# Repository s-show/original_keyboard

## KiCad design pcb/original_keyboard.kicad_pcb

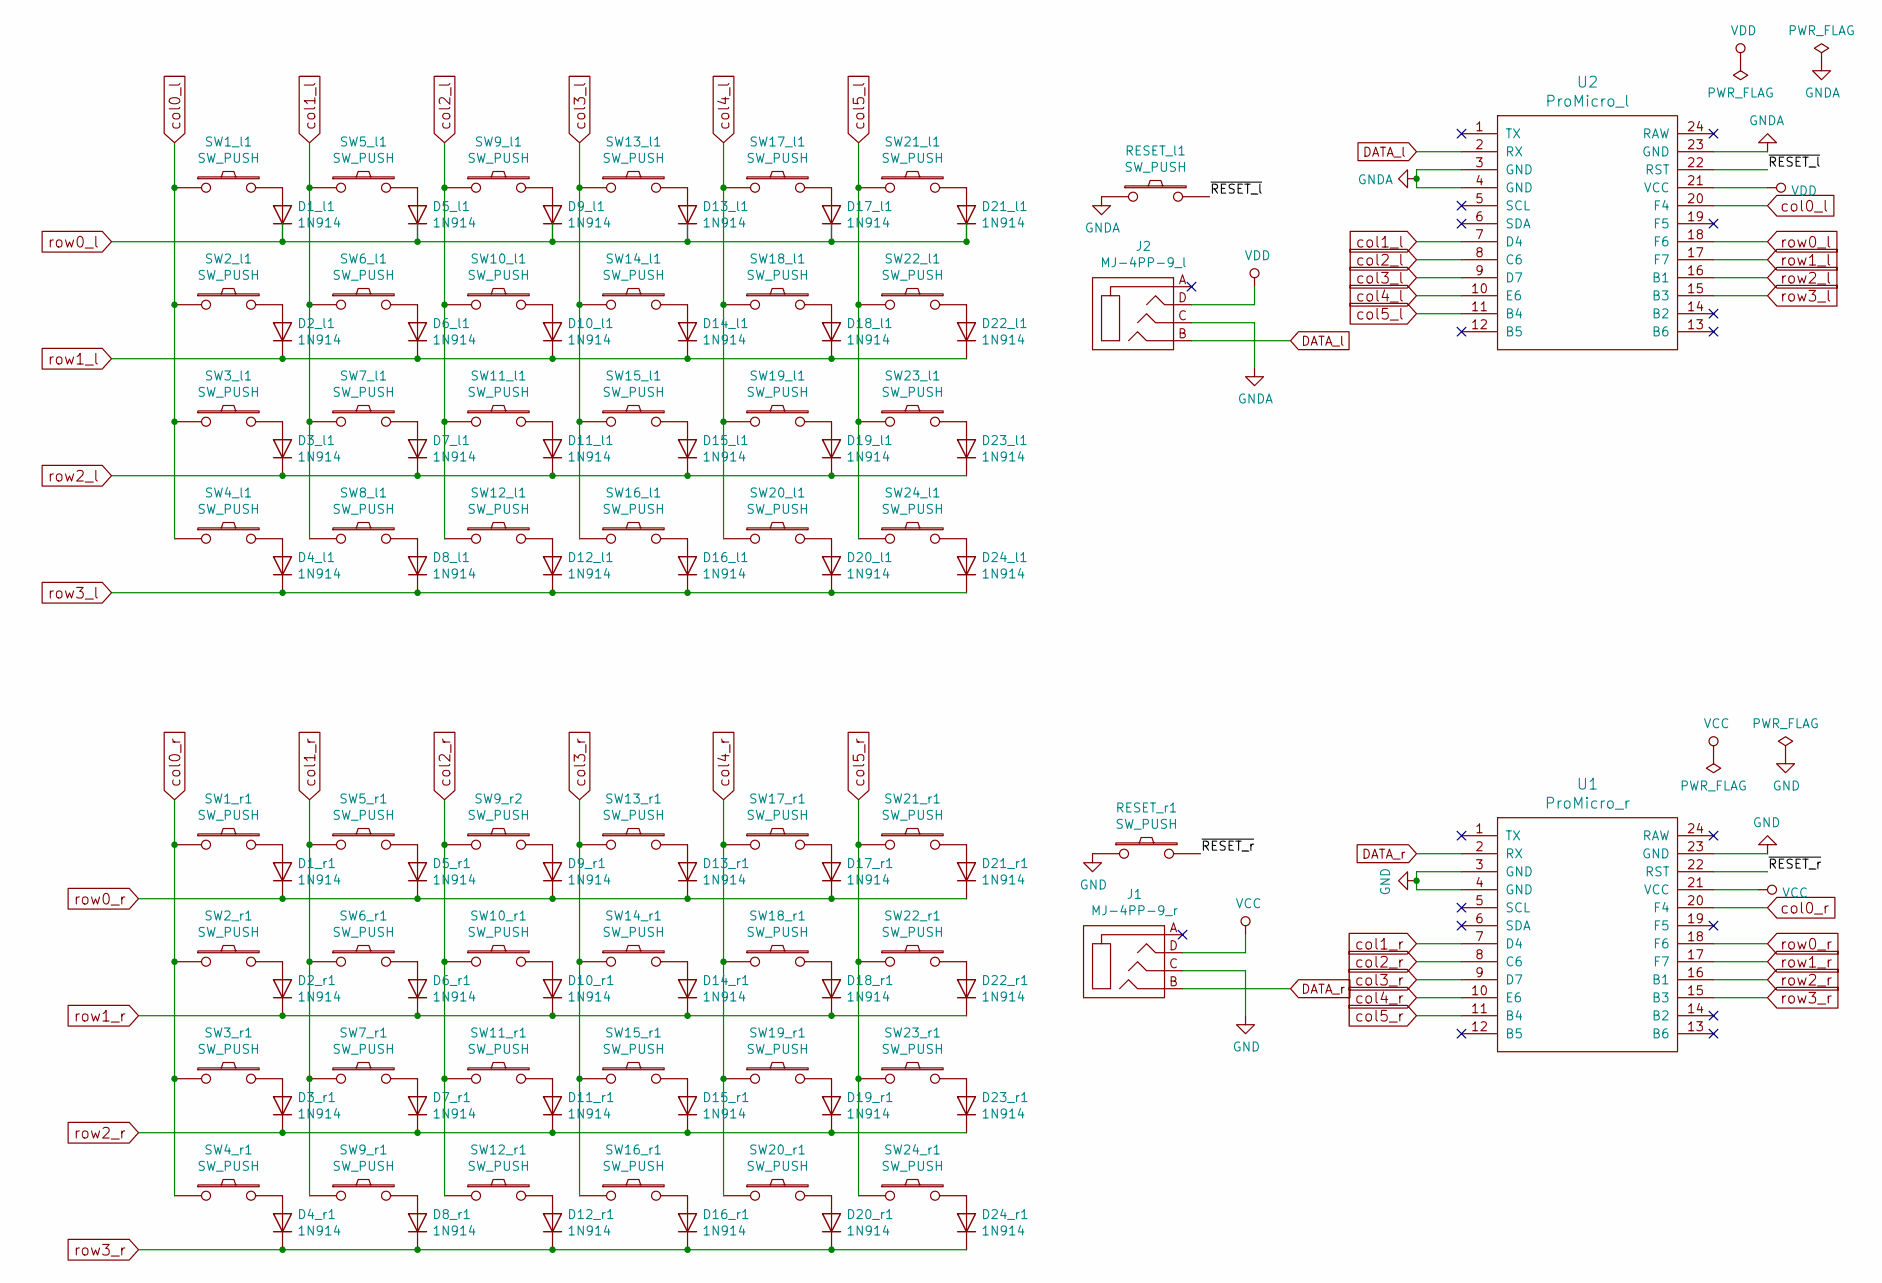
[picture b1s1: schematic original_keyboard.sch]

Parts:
D1_l1, D1_r1, D2_l1, D2_r1, D3_l1, D3_r1, D4_l1, D4_r1, D5_l1, D5_r1, D6_l1, D6_r1, D7_l1, D7_r1, D8_l1, D8_r1, D9_l1, D9_r1, D10_l1, D10_r1, D11_l1, D11_r1, D12_l1, D12_r1, D13_l1, D13_r1, D14_l1, D14_r1, D15_l1, D15_r1, D16_l1, D16_r1, D17_l1, D17_r1, D18_l1, D18_r1, D19_l1, D19_r1, D20_l1, D20_r1, D21_l1, D21_r1, D22_l1, D22_r1, D23_l1, D23_r1, D24_l1, D24_r1: 1N914; D3_TH
J1: MJ-4PP-9_r; MJ-4PP-9_1side
J2: MJ-4PP-9_l; MJ-4PP-9_1side
RESET_l1: SW_PUSH; ResetSW_1side
RESET_r1: SW_PUSH; ResetSW_1side
SW1_l1, SW1_r1, SW2_l1, SW2_r1, SW3_l1, SW3_r1, SW4_l1, SW4_r1, SW5_l1, SW5_r1, SW6_l1, SW6_r1, SW7_l1, SW7_r1, SW8_l1, SW9_l1, SW9_r1, SW9_r2, SW10_l1, SW10_r1, SW11_l1, SW11_r1, SW12_l1, SW12_r1, SW13_l1, SW13_r1, SW14_l1, SW14_r1, SW15_l1, SW15_r1, SW16_l1, SW16_r1, SW17_l1, SW17_r1, SW18_l1, SW18_r1, SW19_l1, SW19_r1, SW20_l1, SW20_r1, SW21_l1, SW21_r1, SW22_l1, SW22_r1, SW23_l1, SW23_r1, SW24_l1, SW24_r1: SW_PUSH; SW_MX
U1: ProMicro_r; ProMicro_v2_1side
U2: ProMicro_l; ProMicro_v2_1side

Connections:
/~RESET_l: RESET_l1.2, U2.22 (RST)
/~RESET_r: RESET_r1.2, U1.22 (RST)
DATA_l: J2.B, U2.2 (RX)
DATA_r: J1.B, U1.2 (RX)
GND: J1.C, RESET_r1.1, U1.3 (GND), U1.4 (GND), U1.23 (GND)
GNDA: J2.C, RESET_l1.1, U2.3 (GND), U2.4 (GND), U2.23 (GND)
unnamed: D1_l1.2 (A), SW1_l1.2
unnamed: D1_r1.2 (A), SW1_r1.2
unnamed: D2_l1.2 (A), SW2_l1.2
unnamed: D2_r1.2 (A), SW2_r1.2
unnamed: D3_l1.2 (A), SW3_l1.2
unnamed: D3_r1.2 (A), SW3_r1.2
unnamed: D4_l1.2 (A), SW4_l1.2
unnamed: D4_r1.2 (A), SW4_r1.2
unnamed: D5_l1.2 (A), SW5_l1.2
unnamed: D5_r1.2 (A), SW5_r1.2
unnamed: D6_l1.2 (A), SW6_l1.2
unnamed: D6_r1.2 (A), SW6_r1.2
unnamed: D7_l1.2 (A), SW7_l1.2
unnamed: D7_r1.2 (A), SW7_r1.2
unnamed: D8_l1.2 (A), SW8_l1.2
unnamed: D8_r1.2 (A), SW9_r1.2
unnamed: D9_l1.2 (A), SW9_l1.2
unnamed: D9_r1.2 (A), SW9_r2.2
unnamed: D10_l1.2 (A), SW10_l1.2
unnamed: D10_r1.2 (A), SW10_r1.2
unnamed: D11_l1.2 (A), SW11_l1.2
unnamed: D11_r1.2 (A), SW11_r1.2
unnamed: D12_l1.2 (A), SW12_l1.2
unnamed: D12_r1.2 (A), SW12_r1.2
unnamed: D13_l1.2 (A), SW13_l1.2
unnamed: D13_r1.2 (A), SW13_r1.2
unnamed: D14_l1.2 (A), SW14_l1.2
unnamed: D14_r1.2 (A), SW14_r1.2
unnamed: D15_l1.2 (A), SW15_l1.2
unnamed: D15_r1.2 (A), SW15_r1.2
unnamed: D16_l1.2 (A), SW16_l1.2
unnamed: D16_r1.2 (A), SW16_r1.2
unnamed: D17_l1.2 (A), SW17_l1.2
unnamed: D17_r1.2 (A), SW17_r1.2
unnamed: D18_l1.2 (A), SW18_l1.2
unnamed: D18_r1.2 (A), SW18_r1.2
unnamed: D19_l1.2 (A), SW19_l1.2
unnamed: D19_r1.2 (A), SW19_r1.2
unnamed: D20_l1.2 (A), SW20_l1.2
unnamed: D20_r1.2 (A), SW20_r1.2
unnamed: D21_l1.2 (A), SW21_l1.2
unnamed: D21_r1.2 (A), SW21_r1.2
unnamed: D22_l1.2 (A), SW22_l1.2
unnamed: D22_r1.2 (A), SW22_r1.2
unnamed: D23_l1.2 (A), SW23_l1.2
unnamed: D23_r1.2 (A), SW23_r1.2
unnamed: D24_l1.2 (A), SW24_l1.2
unnamed: D24_r1.2 (A), SW24_r1.2
VCC: J1.D, U1.21 (VCC)
VDD: J2.D, U2.21 (VCC)
col0_l: SW1_l1.1, SW2_l1.1, SW3_l1.1, SW4_l1.1, U2.20 (F4)
col0_r: SW1_r1.1, SW2_r1.1, SW3_r1.1, SW4_r1.1, U1.20 (F4)
col1_l: SW5_l1.1, SW6_l1.1, SW7_l1.1, SW8_l1.1, U2.7 (D4)
col1_r: SW5_r1.1, SW6_r1.1, SW7_r1.1, SW9_r1.1, U1.7 (D4)
col2_l: SW9_l1.1, SW10_l1.1, SW11_l1.1, SW12_l1.1, U2.8 (C6)
col2_r: SW9_r2.1, SW10_r1.1, SW11_r1.1, SW12_r1.1, U1.8 (C6)
col3_l: SW13_l1.1, SW14_l1.1, SW15_l1.1, SW16_l1.1, U2.9 (D7)
col3_r: SW13_r1.1, SW14_r1.1, SW15_r1.1, SW16_r1.1, U1.9 (D7)
col4_l: SW17_l1.1, SW18_l1.1, SW19_l1.1, SW20_l1.1, U2.10 (E6)
col4_r: SW17_r1.1, SW18_r1.1, SW19_r1.1, SW20_r1.1, U1.10 (E6)
col5_l: SW21_l1.1, SW22_l1.1, SW23_l1.1, SW24_l1.1, U2.11 (B4)
col5_r: SW21_r1.1, SW22_r1.1, SW23_r1.1, SW24_r1.1, U1.11 (B4)
row0_l: D1_l1.1 (K), D5_l1.1 (K), D9_l1.1 (K), D13_l1.1 (K), D17_l1.1 (K), D21_l1.1 (K), U2.18 (F6)
row0_r: D1_r1.1 (K), D5_r1.1 (K), D9_r1.1 (K), D13_r1.1 (K), D17_r1.1 (K), D21_r1.1 (K), U1.18 (F6)
row1_l: D2_l1.1 (K), D6_l1.1 (K), D10_l1.1 (K), D14_l1.1 (K), D18_l1.1 (K), D22_l1.1 (K), U2.17 (F7)
row1_r: D2_r1.1 (K), D6_r1.1 (K), D10_r1.1 (K), D14_r1.1 (K), D18_r1.1 (K), D22_r1.1 (K), U1.17 (F7)
row2_l: D3_l1.1 (K), D7_l1.1 (K), D11_l1.1 (K), D15_l1.1 (K), D19_l1.1 (K), D23_l1.1 (K), U2.16 (B1)
row2_r: D3_r1.1 (K), D7_r1.1 (K), D11_r1.1 (K), D15_r1.1 (K), D19_r1.1 (K), D23_r1.1 (K), U1.16 (B1)
row3_l: D4_l1.1 (K), D8_l1.1 (K), D12_l1.1 (K), D16_l1.1 (K), D20_l1.1 (K), D24_l1.1 (K), U2.15 (B3)
row3_r: D4_r1.1 (K), D8_r1.1 (K), D12_r1.1 (K), D16_r1.1 (K), D20_r1.1 (K), D24_r1.1 (K), U1.15 (B3)

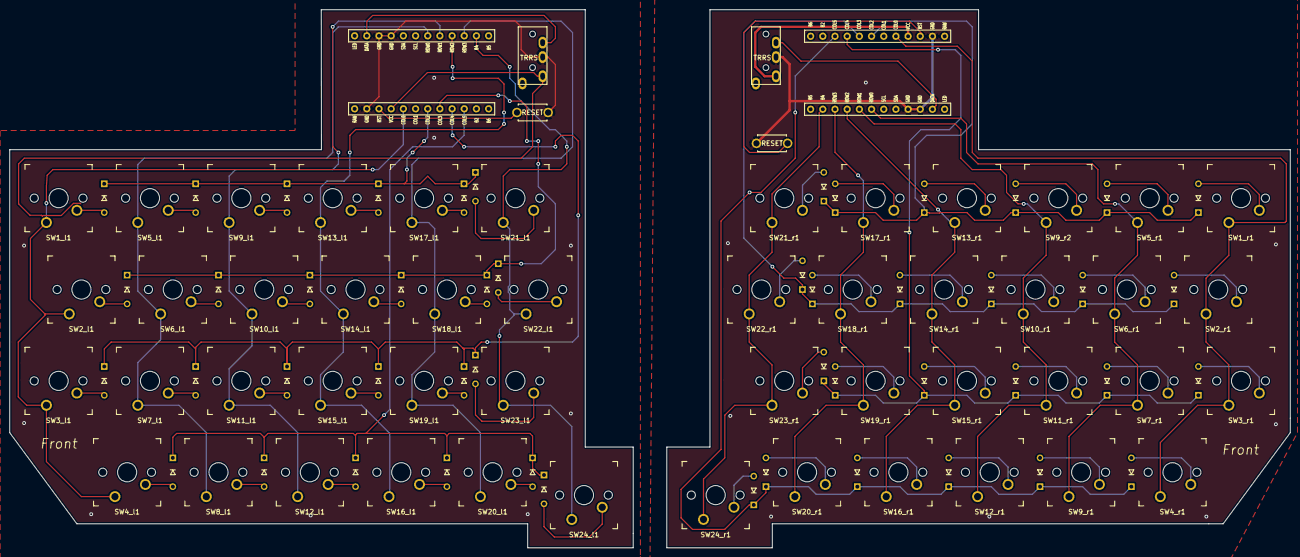
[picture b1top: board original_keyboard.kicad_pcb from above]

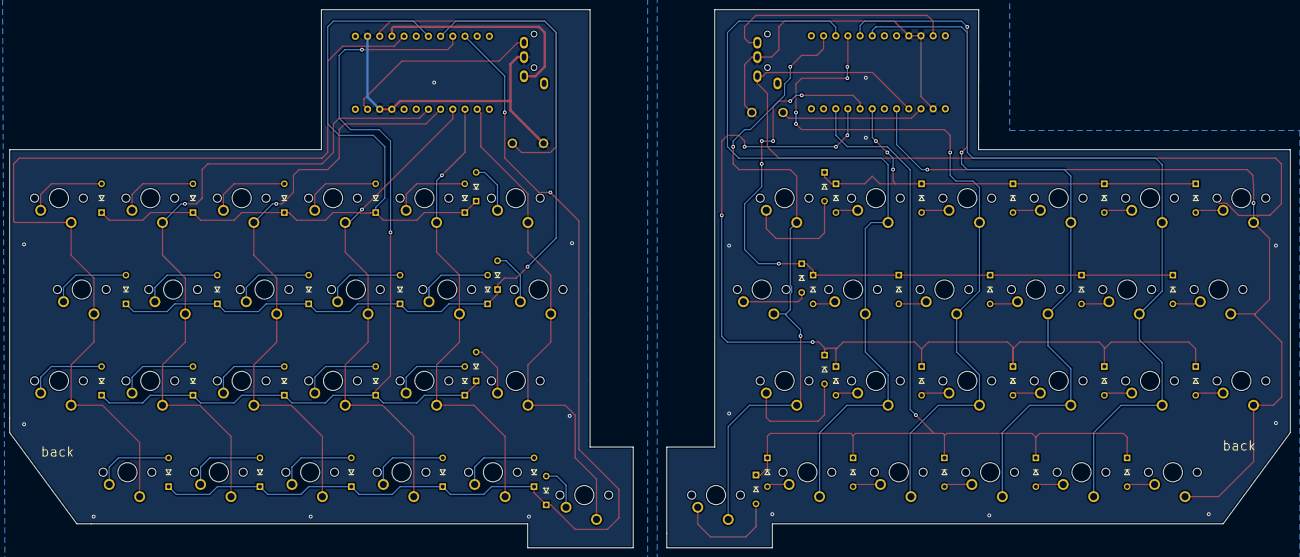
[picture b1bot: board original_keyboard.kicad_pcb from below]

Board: 2 copper layers, 267.0 x 112.2 mm, 102 parts (48 on the bottom side), 76 nets.

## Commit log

2020-04-19 First commit.
2020-05-20 create case_ver2.
